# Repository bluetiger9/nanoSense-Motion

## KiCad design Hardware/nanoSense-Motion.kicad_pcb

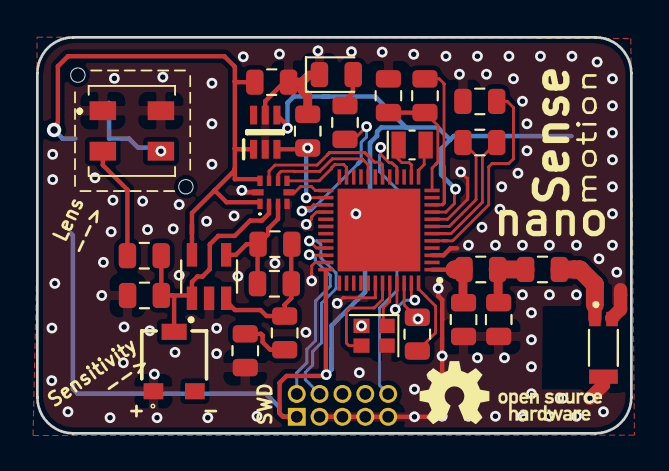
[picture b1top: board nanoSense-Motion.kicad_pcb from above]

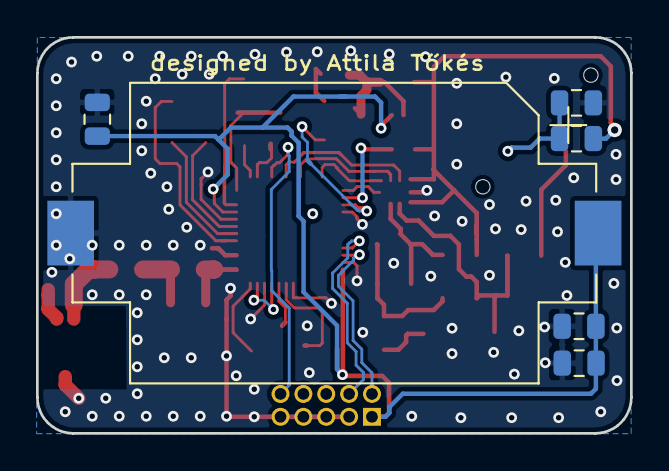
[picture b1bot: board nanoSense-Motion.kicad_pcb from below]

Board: 2 copper layers, 33.0 x 22.0 mm, 36 parts (6 on the bottom side), 33 nets.

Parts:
AE1: W3008; ANTENNA_W3008
BT1: Battery_Cell; BatteryHolder_Keystone_1060_1x2032
C1, C6: 4.7uF; C_0805_2012Metric
C2, C4: 2.2pF; C_0805_2012Metric
C3: 100pF; C_0805_2012Metric
C5, C7, C10: 1uF; C_0805_2012Metric
C8: 2.2uF; C_0805_2012Metric
C9: 15nF; C_0805_2012Metric
C11: 1u; C_0805_2012Metric
C12: 22n; C_0805_2012Metric
C13: 0.1u; C_0805_2012Metric
D1: LED_Small; LED_0805_2012Metric
IC1: PL-N823-01; PLN82301
IC2: NCH-RSL10-101Q48-ABG; QFN40P600X600X100-49N
IC3: ADS7142IRUGR; ADS1018IRUGT
IC4: SIP32431DR3-T1GE3; SOT65P210X110-6N
J1: Conn_02x05_Odd_Even; jtag-10-pin
L1: 4.0nH; L_0805_2012Metric
L2: 3.1nH; L_0805_2012Metric
L3: 2.2uH; L_0805_2012Metric
R1, R3: 10k; R_0805_2012Metric
R2: 28k; R_0805_2012Metric
R4: 100; R_0805_2012Metric
R5: 16k; R_0805_2012Metric
R6: 3.3k; R_0805_2012Metric
R7: 100k; R_0805_2012Metric
RV1: 2M; PVG3A
U1: BU7265; SOT95P280X125-5N
Y1: 32.768kHz; Crystal_SMD_MicroCrystal_CC8V-T1A-2Pin_2.0x1.2mm
Y2: 48Mhz; Crystal_SMD_2016-4Pin_2.0x1.6mm
svg2mod: G***; oshw-logo-2

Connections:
+BATT: BT1.1, C1.1, C3.1, C10.1, IC2.9, IC2.36, IC4.4, J1.1
Alert: IC2.23, IC3.6
AnalogPowerEnable: IC2.26, IC4.3, R7.1
GND: AE1.1, BT1.2, C1.2, C2.2, C3.2, C4.2, C5.2, C6.2, C8.2, C9.2, C10.2, C11.2, C13.2, D1.1, IC1.1, IC1.4, IC2.3, IC2.8, IC2.28, IC2.35, IC2.42, IC2.46, IC3.4, IC3.10, IC4.2, IC4.5, J1.3, J1.5, J1.7, J1.9, R3.2, R7.2, RV1.1, U1.2, Y2.2, Y2.4
unnamed: AE1.2, L1.2
unnamed: C2.1, L1.1, L2.2
unnamed: C4.1, IC2.1, L2.1
unnamed: C5.1, IC2.5
unnamed: C6.1, IC2.12, L3.2
unnamed: C7.1, IC2.6
unnamed: C7.2, IC2.7
unnamed: C8.1, IC2.48
unnamed: C9.1, IC3.2, R1.1, RV1.2, U1.1
unnamed: C11.1, R5.2
unnamed: C12.1, R5.1, R6.1, U1.3
unnamed: C12.2, IC3.3, R6.2, U1.4
unnamed: D1.2, R4.1
unnamed: IC1.2, R1.2
unnamed: IC1.3, R2.2, R3.1
unnamed: IC2.10, L3.1
unnamed: IC2.13, Y1.2
unnamed: IC2.14, Y1.1
unnamed: IC2.27, R4.2
unnamed: IC2.43, Y2.3
unnamed: IC2.44, Y2.1
unnamed: IC2.45, IC2.47
RESET: IC2.16, J1.10
Ready: IC2.25, IC3.5
SCL: IC2.18, IC3.8
SDA: IC2.20, IC3.7
SWCLK: IC2.33, J1.4
SWDIO: IC2.34, J1.2
VDDA: C13.1, IC3.1, IC3.9, IC4.1, R2.1, U1.5

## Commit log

2020-02-27 initial commmit
2020-03-01 blinky + BLE
2020-03-01 KiCad files
2020-03-01 ADS7142 driver (attempt)
2020-03-01 move Firmware to separate folder
2020-03-29 1. ADS7142 driver update 2. interfacing with the RSL10 Sense app 3. ADS7142 autonomous monitoring + RSL10 sleep modes
